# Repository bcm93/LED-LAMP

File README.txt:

AUTORES
	Belén Cebrián
	Sonia Escorza

Proyecto realizado por estudiantes de Grado en Ingeniería de Tecnologías y Servicios
de Telecomunicación en la Universidad de Zaragoza, España.

Junio 2016
----------------------------------------------------------------------------------------------------------------------------------------------------------------

Documentación

Este proyecto trata de una pelota luminosa con distintos modos de juego controlados a
partir de una App para Android. 

Para el diseño de la PCB todos los ficheros necesarios se encuentran en la carpeta ball lamp.

Para la alimentación se utilizan 3 pilas AA pero se podría ampliar este proyecto incluyendo una 
bateria, una red de carga y unos módulos de carga inductiva.Para ello, se necesitaría una base 
para el módulo transmisor con una red de adaptación para la corriente. El módulo receptor 
se encontraría dentro de la pelota junto con la batería y el circuito de carga.

El archivo BallLampApp.apk es la app Android que controla la bola, está lista para ser instalada.
IMPORTANTE: necesario emparejamiento previo al juego del Bluetooth con el dispositivo que 
	        se vaya a utilizar.
	        En cada modo de juego es necesario conectar el bluetooth, para ello se debe 
	        pulsar en el titulo de dicha pantalla. AL SALIR DE LA PANTALLA EL BLUETOOTH
	        SE DESCONECTA.

----------------------------------------------------------------------------------------------------------------------------------------------------------------

Modos de juego

Lámpara: luz en varios colores

Mascotas: cambios de luz controlados al pulsar los botones

Patata Caliente: cambios de luz a partir de los giros de la pelota. Cuando falta poco para que 
		finalice el juego la pelota empieza a parpadear. Al llegar al tiempo límite
		la pelota se pone roja.

_________________________________________________________________________________________________________

Videos de demostración

Modo Lámpara + Modo Mascotas:

https://www.youtube.com/watch?v=WMpuN2jqb0E

Modo Patata Caliente:

https://www.youtube.com/watch?v=RWo7kmP5fRg

-------------------------------------------------------------------------------------------------------------------------------------------------------------

AUTHORS
	Belén Cebrián
	Sonia Escorza

This project has been designed and performed by students of the Degree in Technology and
Telecommunication Services Engineering at the University of Zaragoza, Spain.

June, 2016
----------------------------------------------------------------------------------------------------------------------------------------------------------------

DOCUMENTATION

This project consists of a bright ball with different game modes which can be controlled from
an Android App.

All the necessary files for the design of the PCB are located in the directory "ball lamp".

Three AA batteries are used as energy supply, but the project could be extended to include a
rechargeable battery, a charging network, and inductive charging modules. 
For this, a base for the transmitter module would be needed together with an adapting 
network for the current. The receiver module would be located inside the ball along with the
battery and the charging circuit.

The file named "BallLampApp.apk" is the Android App which controls the ball and it is ready 
to be installed.

IMPORTANT NOTE: It is necessary to previously sincronize the ball with the Bluetooth device 
		which will be used.
		For each game mode, it is necessary to reconnect the bluetooth by clicking 
		on the title of the screen. WHEN YOU LEAVE THE SCREEN, THE BLUETOOTH 
		CONNEXION AUTOMATICALLY DISCONNECTS.

----------------------------------------------------------------------------------------------------------------------------------------------------------------

GAME MODES

"Lámpara" (Lamp): light available in several colors

"Mascotas" (Pets): light changes can be controlled by pressing the buttons

"Patata Caliente": the light changes when the ball rotates. When the game is about to end, 
		the ball starts flashing and it becomes red when the time limit is reached.

----------------------------------------------------------------------------------------------------------------------------------------------------------------

Demostration video

Lamp + Pets:

https://www.youtube.com/watch?v=WMpuN2jqb0E

Patata Caliente:

https://www.youtube.com/watch?v=RWo7kmP5fRg

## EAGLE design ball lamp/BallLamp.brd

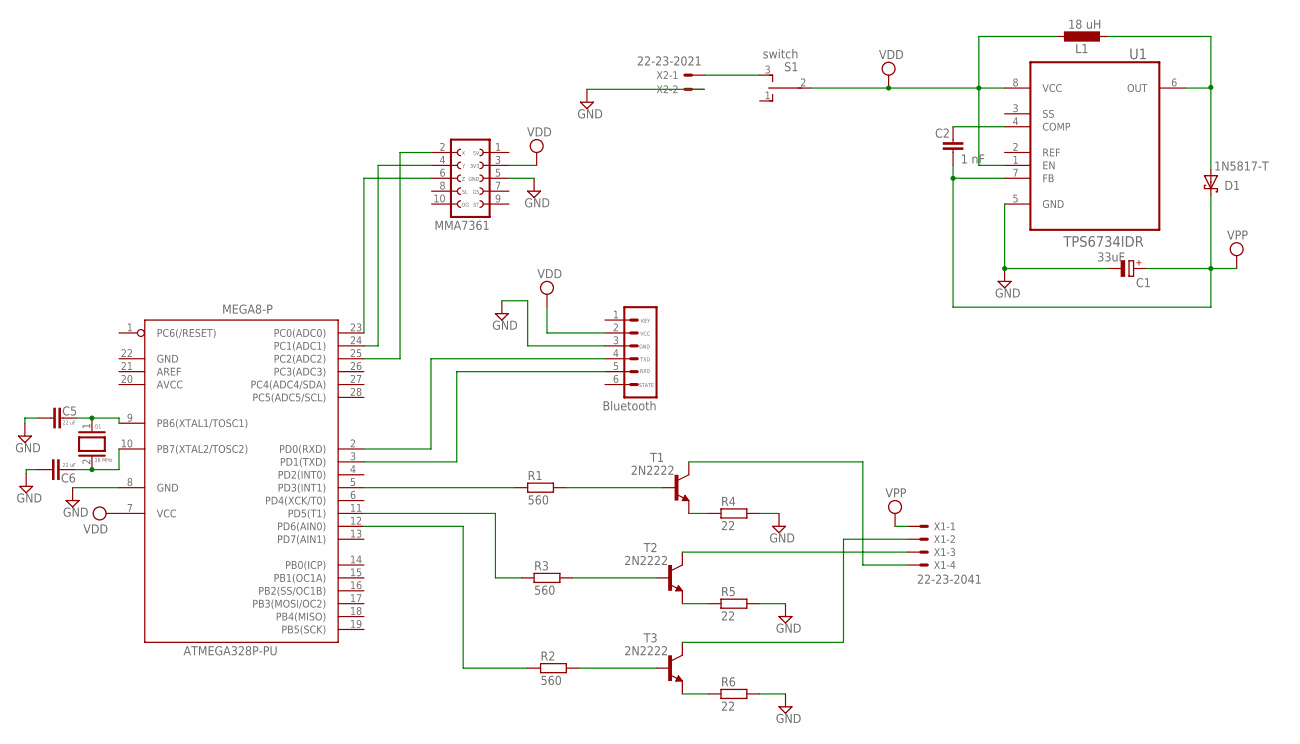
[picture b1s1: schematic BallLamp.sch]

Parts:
ATMEGA328P-PU: MEGA8-P; DIL28-3
BLUETOOTH: M06; 06P
C1: 33uF; E5-5
C2: 1 nF; C025-025X050
C5, C6: 22 uF; C050-024X044
D1: 1N5817-T; DO41-7.6
L1: 18 uH; 0207/10
Q1: 16 MHz; QS
R1, R2, R3: 560; 0207/10
R4, R5, R6: 22; 0207/10
S1: switch; TL3XPO
SV1: FE05-2
T1, T2, T3: 2N2222; TO18
U1: TPS6734IDR; SOIC127P600X175-8N
X1: 22-23-2041
X2: 22-23-2021

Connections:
+12V: C1.+, C2.2, D1.C, U1.7 (FB), X1.1
AVCC: ATMEGA328P-PU.20 (AVCC)
GND: ATMEGA328P-PU.8 (GND), ATMEGA328P-PU.22 (GND), BLUETOOTH.3, C1.-, C5.1, C6.1, R4.2, R5.2, R6.2, SV1.5 (GND), U1.5 (GND), X2.2
unnamed: ATMEGA328P-PU.2 (PD0(RXD)), BLUETOOTH.4
unnamed: ATMEGA328P-PU.3 (PD1(TXD)), BLUETOOTH.5
unnamed: ATMEGA328P-PU.23 (PC0(ADC0)), SV1.6 (Z)
unnamed: ATMEGA328P-PU.24 (PC1(ADC1)), SV1.4 (Y)
unnamed: ATMEGA328P-PU.25 (PC2(ADC2)), SV1.2 (X)
unnamed: ATMEGA328P-PU.5 (PD3(INT1)), R1.1
unnamed: ATMEGA328P-PU.12 (PD6(AIN0)), R2.1
unnamed: ATMEGA328P-PU.11 (PD5(T1)), R3.1
unnamed: R1.2, T1.2 (B)
unnamed: R3.2, T2.2 (B)
unnamed: R6.1, T3.1 (E)
unnamed: R2.2, T3.2 (B)
unnamed: R5.1, T2.1 (E)
unnamed: R4.1, T1.1 (E)
unnamed: T1.3 (C), X1.4
unnamed: T3.3 (C), X1.2
unnamed: T2.3 (C), X1.3
unnamed: D1.A, L1.2, U1.6 (OUT)
unnamed: S1.3 (S), X2.1
unnamed: C2.1, U1.4 (COMP)
unnamed: ATMEGA328P-PU.10 (PB7(XTAL2/TOSC2)), C6.2, Q1.2
unnamed: ATMEGA328P-PU.9 (PB6(XTAL1/TOSC1)), C5.2, Q1.1
VDD: ATMEGA328P-PU.7 (VCC), BLUETOOTH.2, L1.1, S1.2, SV1.3 (3V3), U1.1 (EN), U1.8 (VCC)

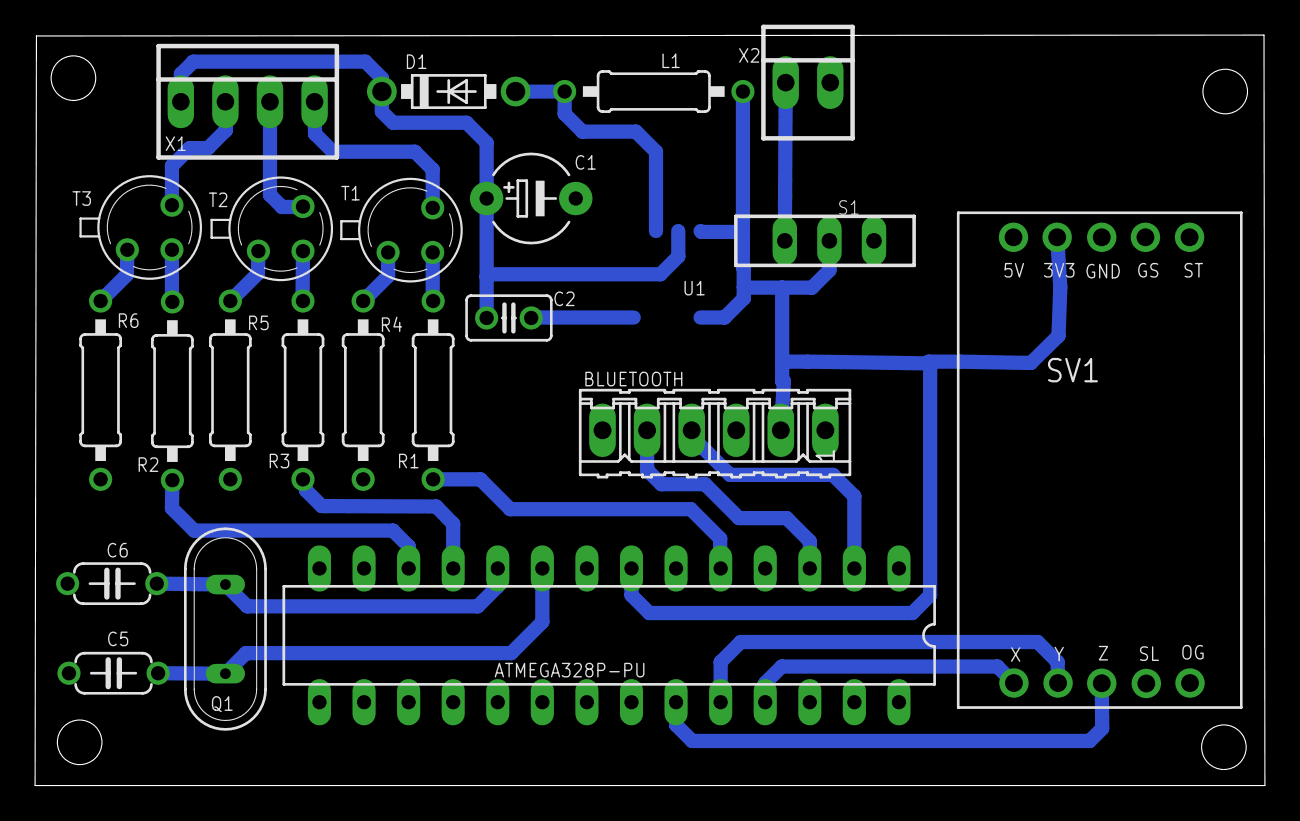
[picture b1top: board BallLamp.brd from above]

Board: 2 copper layers, 70.1 x 42.8 mm, 23 parts (1 on the bottom side), 25 nets.

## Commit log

2016-06-22 LED LAMP
